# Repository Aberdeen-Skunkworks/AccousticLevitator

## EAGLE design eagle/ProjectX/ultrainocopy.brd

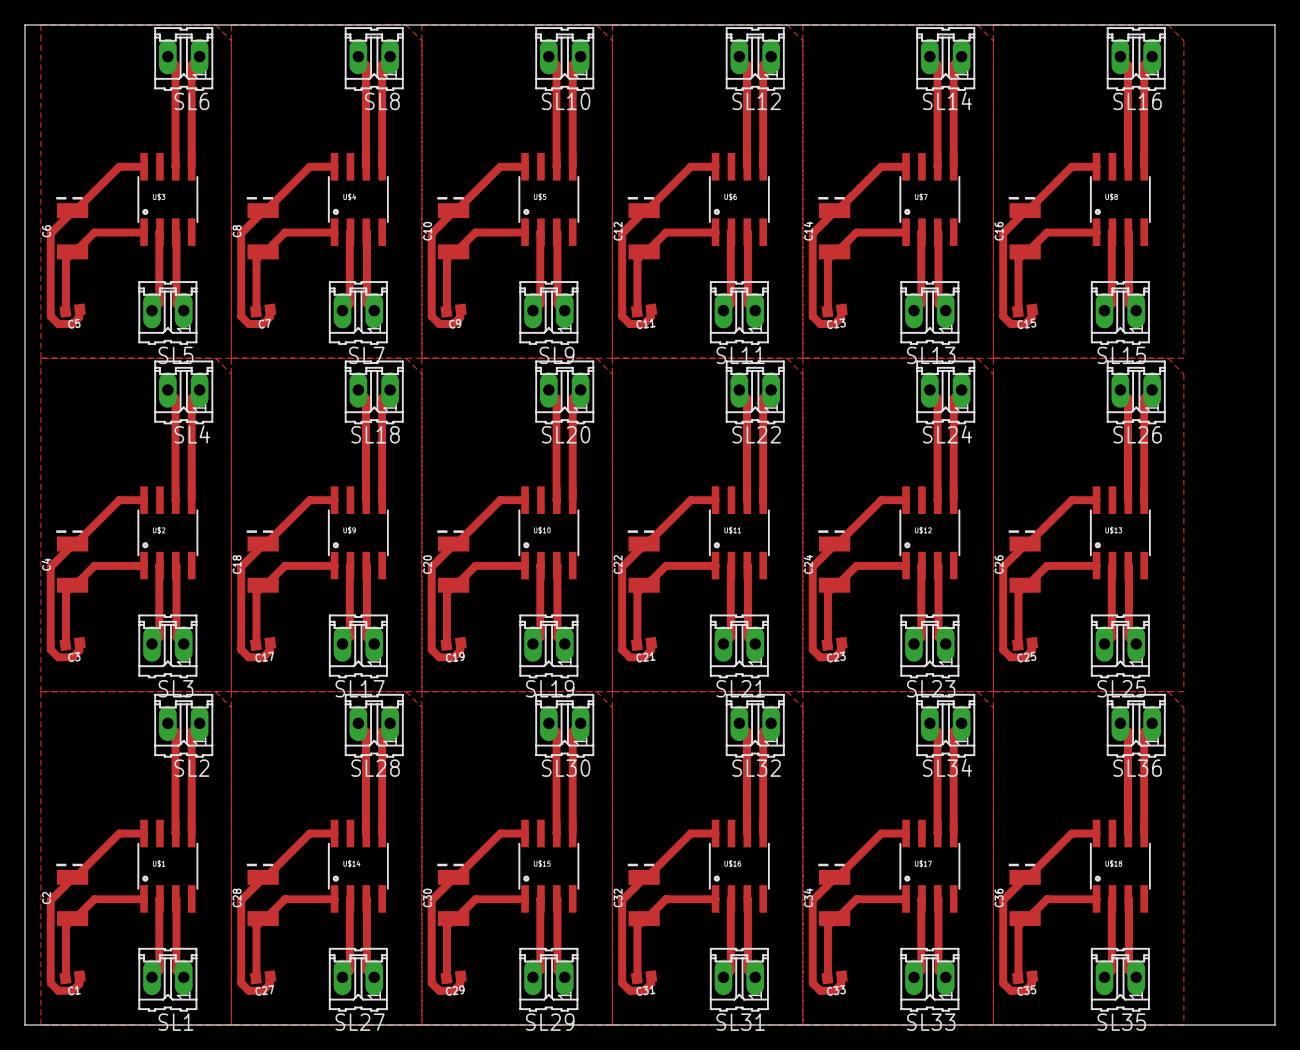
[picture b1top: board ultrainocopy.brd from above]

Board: 2 copper layers, 100.0 x 80.0 mm, 90 parts (0 on the bottom side), 108 nets.

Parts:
C1, C3, C5, C7, C9, C11, C13, C15, C17, C19, C21, C23, C25, C27, C29, C31, C33, C35: 0.1uF; 0402
C2, C4, C6, C8, C10, C12, C14, C16, C18, C20, C22, C24, C26, C28, C30, C32, C34, C36: 47uF; EIA3528
SL1, SL2, SL3, SL4, SL5, SL6, SL7, SL8, SL9, SL10, SL11, SL12, SL13, SL14, SL15, SL16, SL17, SL18, SL19, SL20, SL21, SL22, SL23, SL24, SL25, SL26, SL27, SL28, SL29, SL30, SL31, SL32, SL33, SL34, SL35, SL36: 02P
U$1, U$2, U$3, U$4, U$5, U$6, U$7, U$8, U$9, U$10, U$11, U$12, U$13, U$14, U$15, U$16, U$17, U$18: TC4427; SOIC-8

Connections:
GND: C1.1, C2.A, U$1.8
GND1: C3.1, C4.A, U$2.8
GND2: C5.1, C6.A, U$3.8
GND3: C7.1, C8.A, U$4.8
GND4: C9.1, C10.A, U$5.8
GND5: C11.1, C12.A, U$6.8
GND6: C13.1, C14.A, U$7.8
GND7: C15.1, C16.A, U$8.8
GND8: C17.1, C18.A, U$9.8
GND9: C19.1, C20.A, U$10.8
GND10: C21.1, C22.A, U$11.8
GND11: C23.1, C24.A, U$12.8
GND12: C25.1, C26.A, U$13.8
GND13: C27.1, C28.A, U$14.8
GND14: C29.1, C30.A, U$15.8
GND15: C31.1, C32.A, U$16.8
GND16: C33.1, C34.A, U$17.8
GND17: C35.1, C36.A, U$18.8
unnamed: SL1.2, U$1.2
unnamed: SL1.1, U$1.3
unnamed: SL2.1, U$1.5
unnamed: SL2.2, U$1.6
unnamed: SL3.2, U$2.2
unnamed: SL3.1, U$2.3
unnamed: SL4.1, U$2.5
unnamed: SL4.2, U$2.6
unnamed: SL5.2, U$3.2
unnamed: SL5.1, U$3.3
unnamed: SL6.1, U$3.5
unnamed: SL6.2, U$3.6
unnamed: SL7.2, U$4.2
unnamed: SL7.1, U$4.3
unnamed: SL8.1, U$4.5
unnamed: SL8.2, U$4.6
unnamed: SL9.2, U$5.2
unnamed: SL9.1, U$5.3
unnamed: SL10.1, U$5.5
unnamed: SL10.2, U$5.6
unnamed: SL11.2, U$6.2
unnamed: SL11.1, U$6.3
unnamed: SL12.1, U$6.5
unnamed: SL12.2, U$6.6
unnamed: SL13.2, U$7.2
unnamed: SL13.1, U$7.3
unnamed: SL14.1, U$7.5
unnamed: SL14.2, U$7.6
unnamed: SL15.2, U$8.2
unnamed: SL15.1, U$8.3
unnamed: SL16.1, U$8.5
unnamed: SL16.2, U$8.6
unnamed: SL17.2, U$9.2
unnamed: SL17.1, U$9.3
unnamed: SL18.1, U$9.5
unnamed: SL18.2, U$9.6
unnamed: SL19.2, U$10.2
unnamed: SL19.1, U$10.3
unnamed: SL20.1, U$10.5
unnamed: SL20.2, U$10.6
unnamed: SL21.2, U$11.2
unnamed: SL21.1, U$11.3
unnamed: SL22.1, U$11.5
unnamed: SL22.2, U$11.6
unnamed: SL23.2, U$12.2
unnamed: SL23.1, U$12.3
unnamed: SL24.1, U$12.5
unnamed: SL24.2, U$12.6
unnamed: SL25.2, U$13.2
unnamed: SL25.1, U$13.3
unnamed: SL26.1, U$13.5
unnamed: SL26.2, U$13.6
unnamed: SL27.2, U$14.2
unnamed: SL27.1, U$14.3
unnamed: SL28.1, U$14.5
unnamed: SL28.2, U$14.6
unnamed: SL29.2, U$15.2
unnamed: SL29.1, U$15.3
unnamed: SL30.1, U$15.5
unnamed: SL30.2, U$15.6
unnamed: SL31.2, U$16.2
unnamed: SL31.1, U$16.3
unnamed: SL32.1, U$16.5
unnamed: SL32.2, U$16.6
unnamed: SL33.2, U$17.2
unnamed: SL33.1, U$17.3
unnamed: SL34.1, U$17.5
unnamed: SL34.2, U$17.6
unnamed: SL35.2, U$18.2
unnamed: SL35.1, U$18.3
unnamed: SL36.1, U$18.5
unnamed: SL36.2, U$18.6
VCC: C1.2, C2.C, U$1.1
VCC1: C3.2, C4.C, U$2.1
VCC2: C5.2, C6.C, U$3.1
VCC3: C7.2, C8.C, U$4.1
VCC4: C9.2, C10.C, U$5.1
VCC5: C11.2, C12.C, U$6.1
VCC6: C13.2, C14.C, U$7.1
VCC7: C15.2, C16.C, U$8.1
VCC8: C17.2, C18.C, U$9.1
VCC9: C19.2, C20.C, U$10.1
VCC10: C21.2, C22.C, U$11.1
VCC11: C23.2, C24.C, U$12.1
VCC12: C25.2, C26.C, U$13.1
VCC13: C27.2, C28.C, U$14.1
VCC14: C29.2, C30.C, U$15.1
VCC15: C31.2, C32.C, U$16.1
VCC16: C33.2, C34.C, U$17.1
VCC17: C35.2, C36.C, U$18.1

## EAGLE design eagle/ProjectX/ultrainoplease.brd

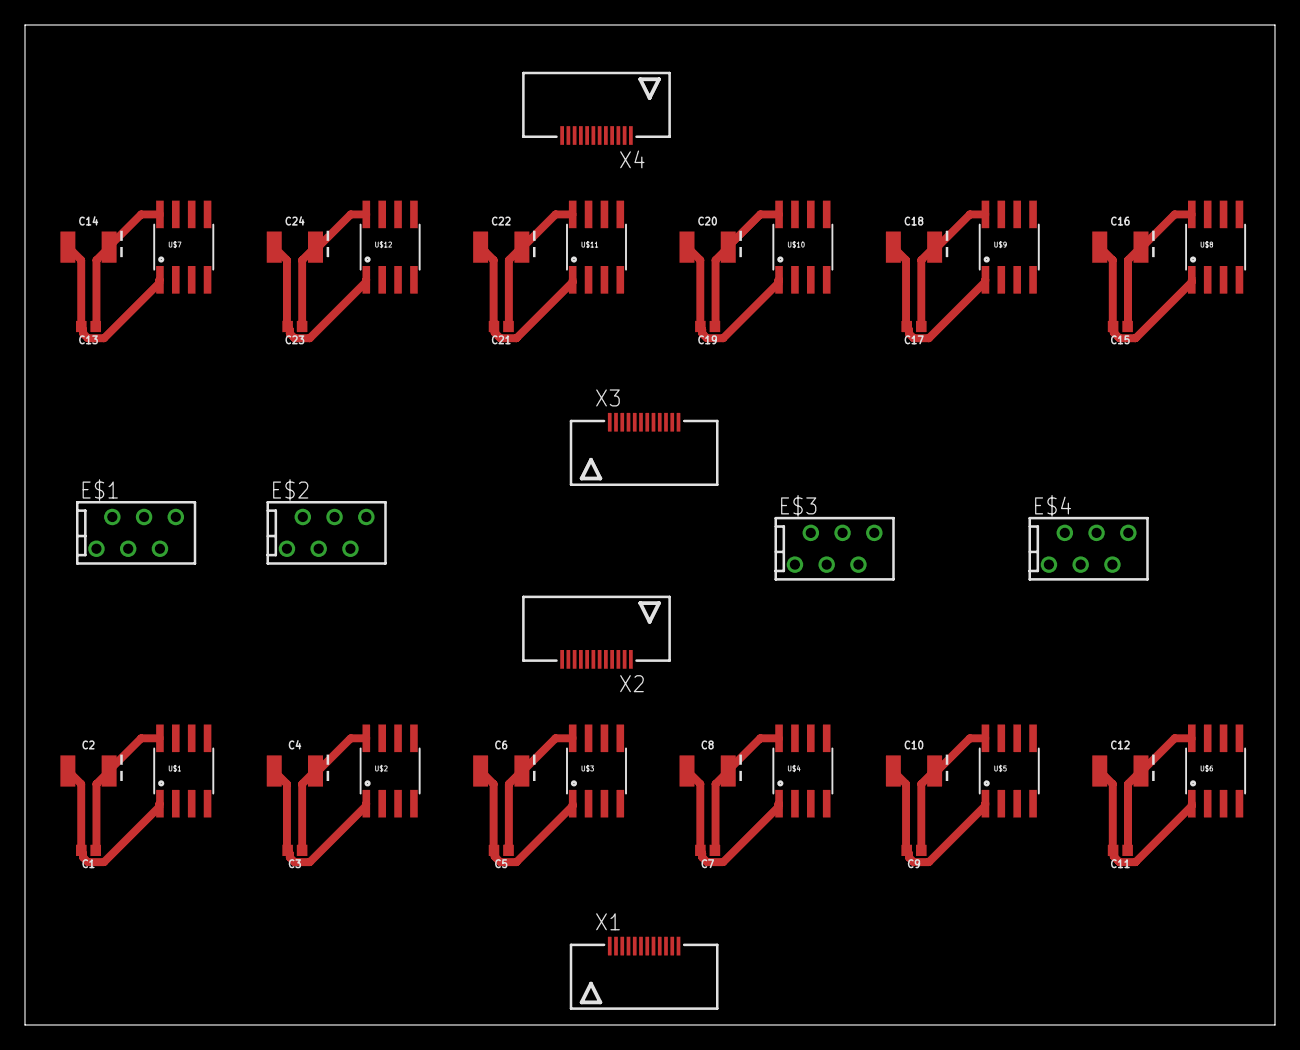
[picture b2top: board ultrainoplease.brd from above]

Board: 2 copper layers, 100.0 x 80.0 mm, 44 parts (0 on the bottom side), 72 nets.

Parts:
C1, C3, C5, C7, C9, C11, C13, C15, C17, C19, C21, C23: 0.1uF; 0402
C2, C4, C6, C8, C10, C12, C14, C16, C18, C20, C22, C24: 47uF; EIA3528
E$1, E$2, E$3, E$4: MTOP-6
U$1, U$2, U$3, U$4, U$5, U$6, U$7, U$8, U$9, U$10, U$11, U$12: TC4427; SOIC-8
X1, X2, X3, X4: 12FLZ-SM1; 12FLZ-SM

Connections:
GND: C1.1, C2.A, U$1.8
GND1: C3.1, C4.A, U$2.8
GND2: C5.1, C6.A, U$3.8
GND3: C7.1, C8.A, U$4.8
GND4: C9.1, C10.A, U$5.8
GND5: C11.1, C12.A, U$6.8
GND6: C13.1, C14.A, U$7.8
GND7: C15.1, C16.A, U$8.8
GND8: C17.1, C18.A, U$9.8
GND9: C19.1, C20.A, U$10.8
GND10: C21.1, C22.A, U$11.8
GND11: C23.1, C24.A, U$12.8
unnamed: U$1.2, X1.1
unnamed: U$1.3, X1.2
unnamed: U$1.5, X2.11
unnamed: U$1.6, X2.12
unnamed: U$2.2, X1.3
unnamed: U$2.3, X1.4
unnamed: U$2.5, X2.9
unnamed: U$2.6, X2.10
unnamed: U$3.2, X1.5
unnamed: U$3.3, X1.6
unnamed: U$3.5, X2.7
unnamed: U$3.6, X2.8
unnamed: U$4.2, X1.7
unnamed: U$4.3, X1.8
unnamed: U$4.5, X2.5
unnamed: U$4.6, X2.6
unnamed: U$5.2, X1.9
unnamed: U$5.3, X1.10
unnamed: U$5.5, X2.3
unnamed: U$5.6, X2.4
unnamed: U$6.2, X1.11
unnamed: U$6.3, X1.12
unnamed: U$6.5, X2.1
unnamed: U$6.6, X2.2
unnamed: U$7.2, X3.1
unnamed: U$7.3, X3.2
unnamed: U$7.5, X4.11
unnamed: U$7.6, X4.12
unnamed: U$8.2, X3.11
unnamed: U$8.3, X3.12
unnamed: U$8.5, X4.1
unnamed: U$8.6, X4.2
unnamed: U$9.2, X3.9
unnamed: U$9.3, X3.10
unnamed: U$9.5, X4.3
unnamed: U$9.6, X4.4
unnamed: U$10.2, X3.7
unnamed: U$10.3, X3.8
unnamed: U$10.5, X4.5
unnamed: U$10.6, X4.6
unnamed: U$11.2, X3.5
unnamed: U$11.3, X3.6
unnamed: U$11.5, X4.7
unnamed: U$11.6, X4.8
unnamed: U$12.2, X3.3
unnamed: U$12.3, X3.4
unnamed: U$12.5, X4.9
unnamed: U$12.6, X4.10
VCC: C1.2, C2.C, U$1.1
VCC1: C3.2, C4.C, U$2.1
VCC2: C5.2, C6.C, U$3.1
VCC3: C7.2, C8.C, U$4.1
VCC4: C9.2, C10.C, U$5.1
VCC5: C11.2, C12.C, U$6.1
VCC6: C13.2, C14.C, U$7.1
VCC7: C15.2, C16.C, U$8.1
VCC8: C17.2, C18.C, U$9.1
VCC9: C19.2, C20.C, U$10.1
VCC10: C21.2, C22.C, U$11.1
VCC11: C23.2, C24.C, U$12.1

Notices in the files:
parts and their libraries:
capacitor: Licensing: Creative Commons ShareAlike 4.0 International - https://creativecommons.org/licenses/by-sa/4.0
